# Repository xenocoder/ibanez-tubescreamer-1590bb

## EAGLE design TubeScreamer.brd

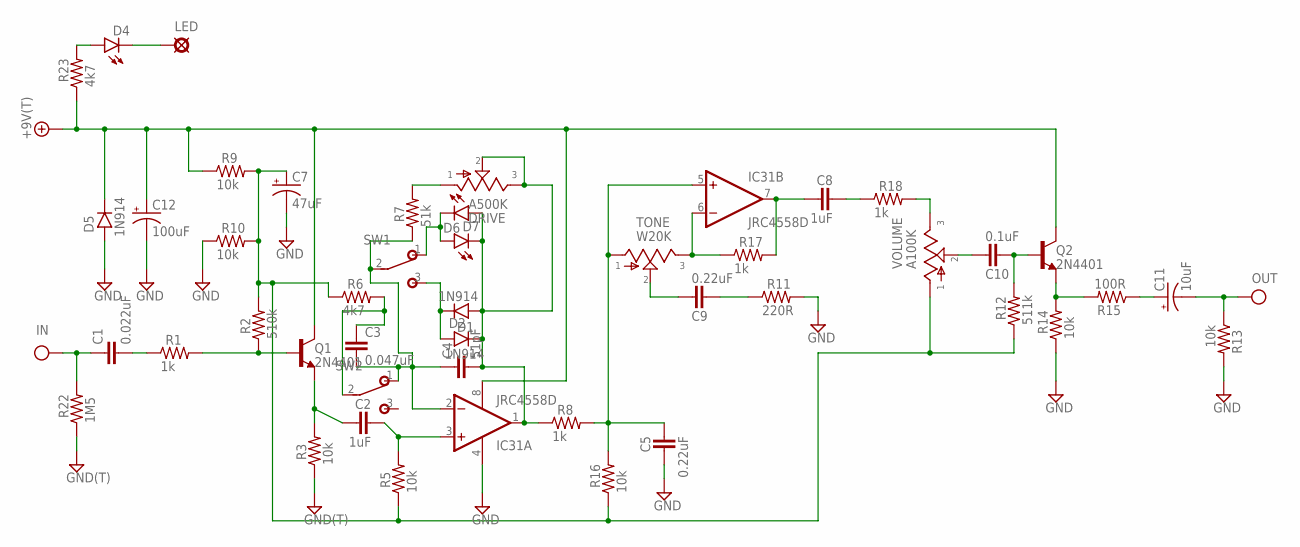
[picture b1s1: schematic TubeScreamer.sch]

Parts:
+9V: +9V(T); SQUARE
C1: 0.022uF; 070X030
C2, C8: 1uF; 072X035
C3: 0.047uF; 070X030
C4: 51pF; 050X030_025
C5, C9: 0.22uF; 072X035
C7: 47uF; 063_025
C10: 0.1uF; 072X035
C11: 10uF; 063_025
C12: 100uF; 080_035
D1, D2, D5: 1N914; DO35-3
D4, D6, D7: LED3MM
DRIVE: A500K; 16MM
GD2: GND(T); SQUARE
GND: GND(T); SQUARE
IC31: JRC4558D; DIL08
IN: IN(T); SQUARE
LED: 3mm; SQUARE
OUT: OUT(T); SQUARE
Q1, Q2: 2N4401; TO92-
R1, R8, R17, R18: 1k; R0207/3
R2: 510k; R0207/3
R3, R5, R9, R10, R13, R14, R16: 10k; R0207/3
R6, R23: 4k7; R0207/3
R7: 51k; R0207/3
R11: 220R; R0207/3
R12: 511k; R0207/3
R15: 100R; R0207/3
R22: 1M5; R0207/3
SW1: DIODES; M9040P
SW2: FAT; M9040P
TONE: W20K; 16MM
VOLUME: A100K; 16MM

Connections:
+9V: +9V.1, C12.+, D5.C, IC31.8 (V+), Q1.1 (C), Q2.1 (C), R9.1, R23.1
GND: C5.1, C7.-, C12.-, D5.A, GD2.1, GND.1, IC31.4 (V-), R3.1, R10.1, R11.2, R13.2, R14.1, R22.1
IN: C1.1, IN.1, R22.2
unnamed: C1.2, R1.1
unnamed: Q1.2 (B), R1.2, R2.1
unnamed: D4.A, R23.2
unnamed: C2.1, Q1.3 (E), R3.2
unnamed: C7.+, R2.2, R5.1, R6.1, R9.2, R10.2, R12.1, R16.1, VOLUME.1
unnamed: C2.2, IC31.3 (+IN), R5.2
unnamed: C4.2, D1.A, D2.C, D6.A, D7.K (C), DRIVE.2, DRIVE.3, IC31.1 (OUT), R8.1
unnamed: C3.1, R6.2, SW2.2
unnamed: DRIVE.1, R7.2
unnamed: C3.2, C4.1, IC31.2 (-IN), R7.1, SW1.2, SW2.1 (O)
unnamed: C9.2, TONE.2
unnamed: C5.2, IC31.5 (+IN), R8.2, R16.2, TONE.1
unnamed: C9.1, R11.1
unnamed: IC31.6 (-IN), R17.1, TONE.3
unnamed: C8.1, IC31.7 (OUT), R17.2
unnamed: C8.2, R18.1
unnamed: R18.2, VOLUME.3
unnamed: C10.2, VOLUME.2
unnamed: C10.1, Q2.2 (B), R12.2
unnamed: Q2.3 (E), R14.2, R15.2
unnamed: C11.+, R15.1
unnamed: D4.K (C), LED.1
unnamed: D1.C, D2.A, SW1.3 (S)
unnamed: D6.K (C), D7.A, SW1.1 (O)
OUT: C11.-, OUT.1, R13.1

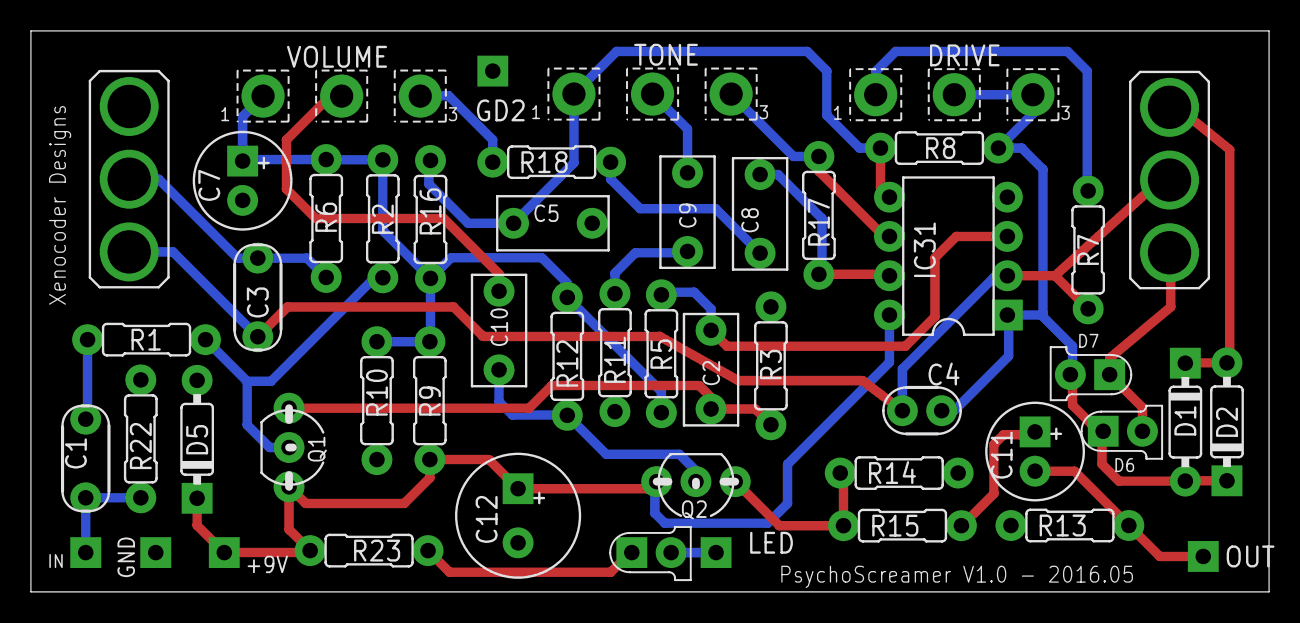
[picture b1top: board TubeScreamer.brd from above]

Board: 2 copper layers, 80.0 x 36.2 mm, 50 parts (0 on the bottom side), 28 nets.

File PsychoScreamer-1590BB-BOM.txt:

Partlist

Exported from TubeScreamer.brd at 8/8/16 7:14 PM

EAGLE Version 7.5.0 Copyright (c) 1988-2015 CadSoft

Assembly variant: 

Part     Value          Package     Library          Position (inch)       Orientation

+9V      +9V(T)         SQUARE      mb_supply        (0.49192913 0.1)      R0
C1       0.022uF        070X030     mb_caps-chicklet (0.13937008 0.33937008) R90
C2       1uF            072X035     mb_caps-box      (1.73031496 0.56535433) R90
C3       0.047uF        070X030     mb_caps-chicklet (0.57716535 0.7492126) R270
C4       51pF           050X030_025 mb_caps-ceramic  (2.26712598 0.46102362) R0
C5       0.22uF         072X035     mb_caps-box      (1.32795276 0.93779528) R180
C7       47uF           063_025     mb_caps-electro  (0.53858268 1.04606299) R270
C8       1uF            072X035     mb_caps-box      (1.85511811 0.96181102) R270
C9       0.22uF         072X035     mb_caps-box      (1.67047244 0.96614173) R90
C10      0.1uF          072X035     mb_caps-box      (1.19094488 0.66496063) R90
C11      10uF           063_025     mb_caps-electro  (2.55472441 0.35708661) R270
C12      100uF          080_035     mb_caps-electro  (1.23937008 0.19370079) R270
D1       1N914          DO35-3      mb_diodes        (2.93700787 0.43188976) R270
D2       1N914          DO35-3      mb_diodes        (3.04291339 0.43267717) R90
D4       LED3MM         LED3MM      mb_diodes        (1.57874016 0.1)      R0
D5       1N914          DO35-3      mb_diodes        (0.42283465 0.38818898) R90
D6       LED3MM         LED3MM      mb_diodes        (2.77795276 0.40866142) R0
D7       LED3MM         LED3MM      mb_diodes        (2.69448819 0.55275591) R180
DRIVE    A500K          16MM        mb_pots          (2.3492126 1.26496063) R180
GD2      GND(T)         SQUARE      mb_supply        (1.175 1.325)         R0
GND      GND(T)         SQUARE      mb_supply        (0.31751969 0.1)      R0
IC31     JRC4558D       DIL08       mb_ics           (2.33425197 0.85433071) R90
IN       IN(T)          SQUARE      mb_supply        (0.13937008 0.1)      R0
LED      3mm            SQUARE      mb_supply        (1.74311024 0.1)      R0
OUT      OUT(T)         SQUARE      mb_supply        (2.98267717 0.09015748) R0
Q1       2N4401         TO92-       mb_trans         (0.65669291 0.36732283) R270
Q2       2N4401         TO92-       mb_trans         (1.69192913 0.28051181) R180
R1       1k             R0207/3     mb_resistors     (0.29409449 0.64173228) R0
R2       510k           R0207/3     mb_resistors     (0.89527559 0.9492126) R90
R3       10k            R0207/3     mb_resistors     (1.88267717 0.57519685) R270
R5       10k            R0207/3     mb_resistors     (1.60393701 0.60590551) R90
R6       4k7            R0207/3     mb_resistors     (0.7511811 0.95)      R270
R7       51k            R0207/3     mb_resistors     (2.68976378 0.87007874) R90
R8       1k             R0207/3     mb_resistors     (2.31141732 1.12913386) R180
R9       10k            R0207/3     mb_resistors     (1.01496063 0.48661417) R90
R10      10k            R0207/3     mb_resistors     (0.88031496 0.48661417) R90
R11      220R           R0207/3     mb_resistors     (1.48582677 0.60866142) R270
R12      511k           R0207/3     mb_resistors     (1.36456693 0.5992126) R270
R13      10k            R0207/3     mb_resistors     (2.64330709 0.16889764) R180
R14      10k            R0207/3     mb_resistors     (2.20905512 0.3023622) R180
R15      100R           R0207/3     mb_resistors     (2.21732283 0.16850394) R180
R16      10k            R0207/3     mb_resistors     (1.01653543 0.9476378) R90
R17      1k             R0207/3     mb_resistors     (2.00472441 0.95787402) R270
R18      1k             R0207/3     mb_resistors     (1.32480315 1.09330709) R180
R22      1M5            R0207/3     mb_resistors     (0.27952756 0.38937008) R270
R23      4k7            R0207/3     mb_resistors     (0.86033465 0.10501969) R0
SW1      DIODES         M9040P      mb_switches      (2.89685039 1.04783465) R180
SW2      FAT            M9040P      mb_switches      (0.25 1.05)           R180
TONE     W20K           16MM        mb_pots          (1.58149606 1.26653543) R180
VOLUME   A100K          16MM        mb_pots          (0.79055118 1.26141732) R180

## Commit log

2016-05-31 Updated Schematic to have FAT and DIODE switch mods on board. Created new PCB layout to fit in 1590BB enclosure.
2016-08-09 Added BOM and PCB png files
2017-12-30 Ran CAM job to get Gerber files for Seeed order
2018-01-04 Made drill layout for 1590BB size board
2018-01-11 Added partslist
2018-01-13 Cleaned up files in directory and added drill guide for 1590BB enclosure
2018-01-13 Added back development files and made a new Dev branch
2018-01-27 Added build guide and updated files
